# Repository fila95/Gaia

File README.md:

# GAIA
Advanced User Interfaces Course Repository

- [GAIA](#gaia)
  * [Configuration](#configuration)
    + [Action Files:](#action-files-)
    + [Actions:](#actions-)
      - [StartAction](#startaction)
          + [Available Attributes](#available-attributes)
      - [End Action](#end-action)
          + [Available Attributes](#available-attributes-1)
      - [Restart Action](#restart-action)
          + [Available Attributes](#available-attributes-2)
      - [Play Audio](#play-audio)
      - [Show Color](#show-color)
      - [Play Animation Action](#play-animation-action)
          + [Available Attributes](#available-attributes-3)
      - [Dynamic Load Action](#dynamic-load-action)
          + [Available Attributes](#available-attributes-4)
      - [Jump Action](#jump-action)
          + [Available Attributes](#available-attributes-5)
      - [Wait Input Action](#wait-input-action)
          + [Available Attributes](#available-attributes-6)
      - [Delay](#delay)
      - [Combined Action](#combined-action)
          + [Available Attributes](#available-attributes-7)
      - [Single Selection Menu Action](#single-selection-menu-action)
      - [Multiple Choice Menu Action](#multiple-choice-menu-action)
          + [Available Attributes](#available-attributes-8)

## Configuration

### Action Files:
Action Files **MUST** contain an array of actions configured as follows:

Remember that the order matters!
``` json
[
	{
		"parseIdentifier": "START",
		"attributes": {}
	},
	{
		"parseIdentifier": "END",
		"attributes": {}
	},
]
```

### Actions:
Actions are composed as follows:
``` json
{
	"parseIdentifier": "START",
	"attributes": {}
}
```

Other two *OPTIONAL* attributes can be specified:
``` json
{
	"parseIdentifier": "START",
	"attributes": {},
	"identifier": "__ID__",
	"timeout": 10
}
```

`identifier` m if specified, sets an identifier for that action so that can be used to the Skip Action.
`timeout` if specified (in seconds), kills the action after a certain amount of time.

#### StartAction
An action that identifies the game's start point.
Start and End actions should be used ONLY in the mail loadable action file!
``` json
{
	"parseIdentifier": "START",
	"attributes": {}
}
```

###### Available Attributes
No attributes are needed.

---

#### End Action
An action that identifies the game has reached the end.
Start and End actions should be used ONLY in the mail loadable action file!
``` json
{
	"parseIdentifier": "END",
	"attributes": {}
}
```

###### Available Attributes
No attributes are needed.

---

#### Restart Action
An action that restarts the entire action hierarchy!
``` json
{
	"parseIdentifier": "RESTART",
	"attributes": {}
}
```

###### Available Attributes
No attributes are needed.

---

#### Play Audio
An action that plays an audio. 
``` json
{
	"parseIdentifier": "PLAY_AUDIO",
	"attributes": {
		"path": "\root\audio_folder\audio.ogg"
	}
}
```
| Parameter 	| Type       	| Description 	|
|-----------	|------------	|-------------	|
| path | `required` 	| path should be a path for a useful audio: `\root\audio_folder\audio.ogg`|

---

#### Show Color
An action that shows a color on a dot.
Colors should be specified if different colors should be applied to different dots.
Color should be specified wether it is needed to update all colors at once.
One of those properties **MUST** be specified!
``` json
{
	"parseIdentifier": "SHOW_COLOR",
	"attributes": {
		"fade": true,
		"colors": [
			{
				"index" : 0,
				"color" : {
					"red":255,
					"green":255,
					"blue":255
				}
			},
			{
				"index" : 1,
				"color" : {
					"red":128,
					"green":128,
					"blue":128
				}
			}
		],
		"color": {
			"red":255,
			"green":255,
			"blue":255
		}
	}
}
```

| Parameter 	| Type       	| Description 	|
|-----------	|------------	|-------------	|
| colors | `required` *one* 	| `color` defines the next color to show, `index` defines the dot that will show the color  |
| color | `required` *one* 	| color sets all the dots to the same color |
| fade | `optional` 	| fade animates the transation between the previous color and the taget ones|

---

#### Play Animation Action
An action that plays an animation on the dots!
If no timeout is specified in the action's definition the action starts and ends immediately so make sure to set the `stops_at_end` key accordingly to your needs!
``` json
{
	"parseIdentifier": "PLAY_ANIMATION",
	"attributes": {
		"animation": "RAINBOW_CYCLE",
		"animation_affect_dots": true,
		"stops_at_end": true
	}
}
```

###### Available Attributes

| Parameter 	| Type       	| Description 	|
|-----------	|------------	|-------------	|
| animation | `required` 	| animation should be one of: `RAINBOW`, `RAINBOW_CYCLE`, `THEATER_CHASE_RAINBOW`|
| animation_affect_dots | `optional` 	| wether animation animates the single leds or the entire dot |
| stops_at_end | `required` 	| when action finishes set `true` if the animation should stop, otherwise set `false`|

---

#### Dynamic Load Action
An action that loads other actions from file and appends them after itself. Then goes directly to the next one.
``` json
{
	"parseIdentifier": "DYNAMIC_LOAD",
	"attributes": {
		"paths": [
			"config/blabla.action.json"
		]
	}
}
```

###### Available Attributes

| Parameter 	| Type       	| Description 	|
|-----------	|------------	|-------------	|
| paths | `required` 	| array of strings identifying one file each|

---

#### Jump Action
An action that jumps to another action given its identifier. Notice that the identifier of the other action **MUST** exist and be present in the current loaded actions hierarchy. Just specify it as you can see [here](#actions-)!
``` json
{
	"parseIdentifier": "JUMP",
	"attributes": {
		"actionIdentifier": "__ID__"
	}
}
```

###### Available Attributes

| Parameter 	| Type       	| Description 	|
|-----------	|------------	|-------------	|
| actionIdentifier | `required` 	| string that identifies another action|

---

#### Wait Input Action
An action that waits for a specified input (all of the specified are tapped) to proceed to the next action.
if `available_dot_indexes` is not specified than it waits for one input to proceed.
``` json
{
	"parseIdentifier": "WAIT_INPUT",
	"attributes": {
		"available_dot_indexes": [
			0,
			1
		]
	}
}
```

###### Available Attributes

| Parameter 	| Type       	| Description 	|
|-----------	|------------	|-------------	|
| available_dot_indexes | `optional` 	| array of integers identifying dots that are allowed to be tapped|

---

#### Delay 
A delay between 2 action.
Timeout should be in **seconds**.
``` json
{
	"parseIdentifier": "DELAY",
	"attributes": {
		"delay": 10
	}
}
```
| Parameter 	| Type       	| Description 	|
|-----------	|------------	|-------------	|
| delay | `required` 	| delay in seconds between 2 actions |

---

#### Combined Action 
Defines multiple action to be executed together.
``` json
{
	"parseIdentifier": "COMBINED",
	"timeout": 10,
	"attributes": {
		"actions": [
			{
				"parseIdentifier": "PLAY_ANIMATION",
				"attributes": {
					"animation": "RAINBOW_CYCLE",
					"animation_affect_dots": true,
					"stops_at_end": true
				}
			},
			{
				"parseIdentifier": "PLAY_AUDIO",
				"attributes": {
					"path": "\root\audio_folder\audio.ogg"
				}
			}
		],
		"policy" : "EXIT_TIMEOUT"
	}
}
```

###### Available Attributes
| Parameter 	| Type       	| Description 	|
|-----------	|------------	|-------------	|
| actions | `required` 	| actions to be executed together. Actions such as `DYNAMIC_LOAD`, `END`, `START`, `RESTART`, `JUMP` are automatically ignored if added! |
| policy | `required` 	| two types of policies: `WAIT_ALL` (waits all actions to be terminated before continuing) ,  `WAIT_FIRST` (when first is completed go to the next action), `EXIT_TIMEOUT` (kills this entire group when timeout occurs)|

---

#### Single Selection Menu Action
A menu which makes people choose between different options. When one is selected its actions are executed!

Options **MUST** contain as many options as dots are in the system!

``` json
{
	"parseIdentifier": "SINGLE_CHOICE_MENU",
	"timeout": 10,
	"attributes": {
		"options": [
			{
				"actions" : [],
				"color" : {
					"red" : "25",
					"green" : "25",
					"blue" : "25"
				}
			}
			{
				"actions" : [],
				"color" : {
					"red" : "25",
					"green" : "25",
					"blue" : "25"
				}
			}
			{
				"actions" : [],
				"color" : {
					"red" : "25",
					"green" : "25",
					"blue" : "25"
				}
			}
			{
				"actions" : [],
				"color" : {
					"red" : "25",
					"green" : "25",
					"blue" : "25"
				}
			}
		],
		"timeout_actions": []
			
	}
}
```

| Parameter 	| Type       	| Description 	|
|-----------	|------------	|-------------	|
| options | `required` 	| options available: `actions` is an array of action objects, `color` is the color associated with that action! Options **MUST** contain as many options as dots are in the system!  |
| timeout_actions | `required` | action object array to be executed after a timeout |

---

#### Multiple Choice Menu Action 
Defines a menu with different options and when one sequence is correctly inserted than it triggers its actions, otherwise it triggers a wrong choices defined action!

Options **MUST** contain as many options as dots are in the system!

``` json
{
	"parseIdentifier": "MULTIPLE_CHOICE_MENU",
	"timeout": 10,
	"attributes": {
		"options": [
			{ "red": 255, "green": 255, "blue": 255 },
			{ "red": 255, "green": 255, "blue": 255 },
			{ "red": 255, "green": 255, "blue": 255 },
			{ "red": 255, "green": 255, "blue": 255 }
		],
		"allowed_sequences": [
			{ 
				"actions": [],
				"chosen_options": [0, 3]
			}
		],
		"wrong_sequence_actions": [],
		"abort_actions": [],
		"time_between_choices": 1
	}
}
```

###### Available Attributes
| Parameter 	| Type       	| Description 	|
|-----------	|------------	|-------------	|
| options | `required` 	| contains an array of colors that will be shown on the dots as choices. The number of options **MUST** be equal to the number of dots! |
| allowed_sequences | `required` | array of items containing a list of actions to be executed when whose options are selected!, `chosen_options` should be an array of integers which reflects the `options` described above. **Remember**: order matters! |
| wrong_sequence_actions | `required` | Sequence of actions that are executed if a not allowed sequence if inserted! |
| abort_actions | `required` | Sequence of actions that are executed when timeout fires and no choice is taken! |
| time_between_choices | `optional` | Maximum time allowed between each tap on dots! if timeout fires up than it checks the inserted sequence and does its things according to the correctness of it. |

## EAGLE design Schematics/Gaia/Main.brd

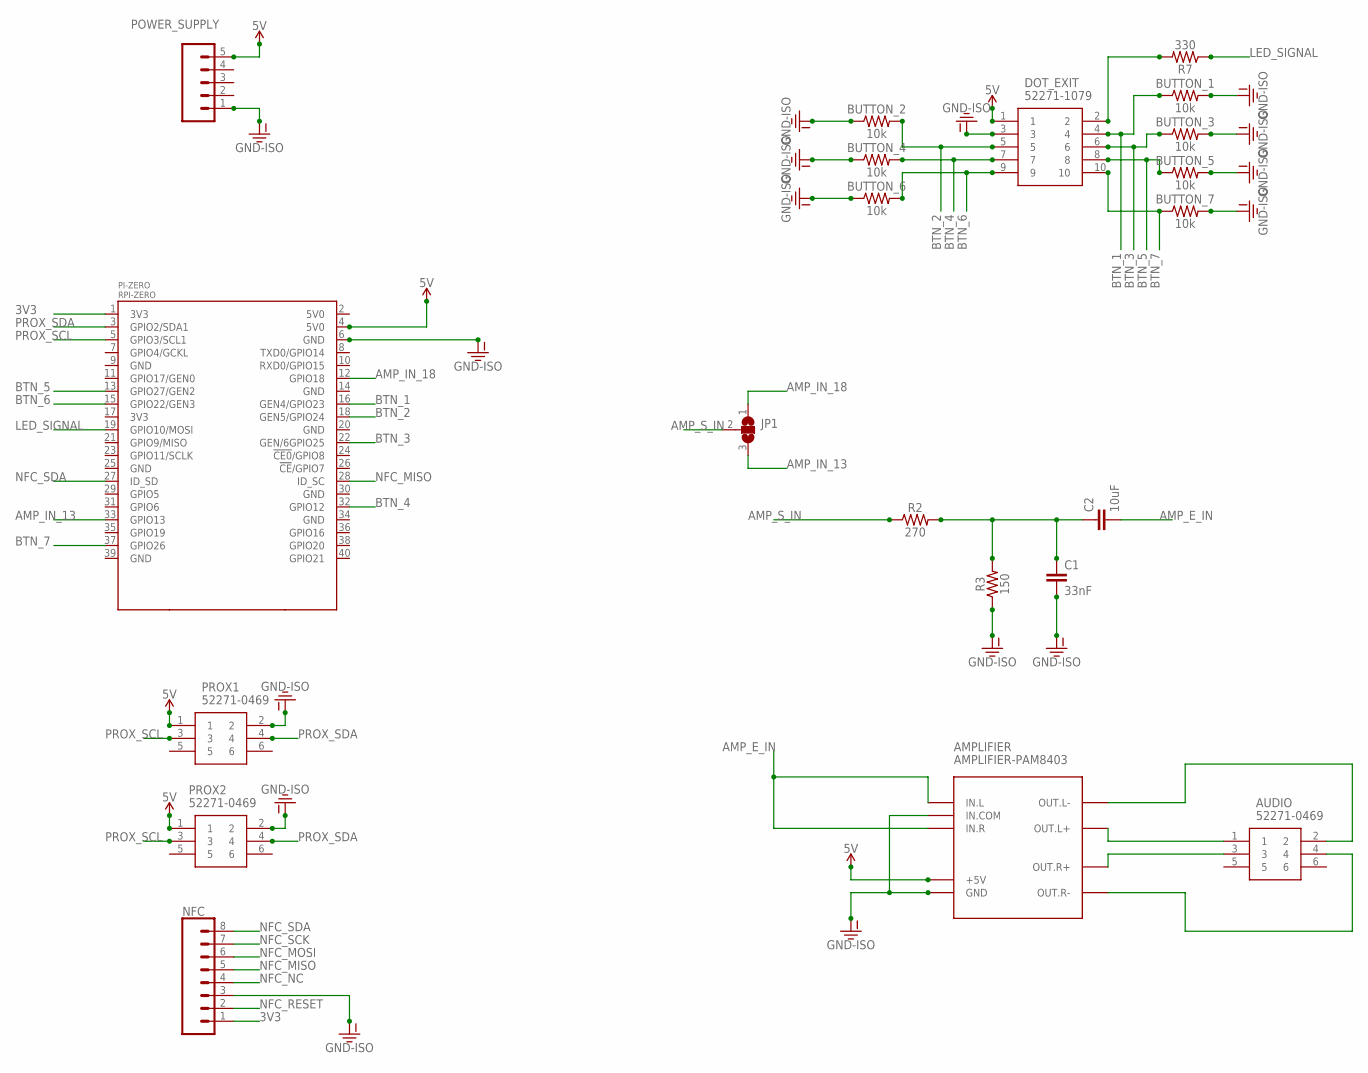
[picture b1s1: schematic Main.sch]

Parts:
AMPLIFIER: AMPLIFIER-PAM8403
AUDIO: 52271-0469; MOLEX_52271-0469
BUTTON_1, BUTTON_2, BUTTON_3, BUTTON_4, BUTTON_5, BUTTON_6, BUTTON_7: 10k; AXIAL-0.3
C1: 33nF; CAP-PTH-10MM
C2: 10uF; CAP-PTH-10MM
DOT_EXIT: 52271-1079
JP1: SJ2W; SJ_2
NFC: CONN_08"; 1X08
PI-ZERO: RPI-ZERO; RASPBERRYPI_BASTELSTUBE_V13_RASPI_BOARD_B+_FULL
POWER_SUPPLY: CONN_05; 1X05
PROX1, PROX2: 52271-0469; MOLEX_52271-0469
R2: 270; AXIAL-0.3
R3: 150; AXIAL-0.3
R7: 330; AXIAL-0.3

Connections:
3V3: NFC.1, PI-ZERO.1 (3V3)
5V: AMPLIFIER.+5V, DOT_EXIT.1, PI-ZERO.4 (5V0), POWER_SUPPLY.5, PROX1.1, PROX2.1
AMP_E_IN: AMPLIFIER.IN.L, AMPLIFIER.IN.R, C2.2
AMP_IN_13: JP1.3, PI-ZERO.33 (GPIO13)
AMP_IN_18: JP1.1, PI-ZERO.12 (GPIO18)
AMP_S_IN: JP1.2, R2.P$1 (1)
BTN_1: BUTTON_1.P$1 (1), DOT_EXIT.4, PI-ZERO.16 (GEN4/GPIO23)
BTN_2: BUTTON_2.P$2 (2), DOT_EXIT.5, PI-ZERO.18 (GEN5/GPIO24)
BTN_3: BUTTON_3.P$1 (1), DOT_EXIT.6, PI-ZERO.22 (GEN/6GPIO25)
BTN_4: BUTTON_4.P$2 (2), DOT_EXIT.7, PI-ZERO.32 (GPIO12)
BTN_5: BUTTON_5.P$1 (1), DOT_EXIT.8, PI-ZERO.13 (GPIO27/GEN2)
BTN_6: BUTTON_6.P$2 (2), DOT_EXIT.9, PI-ZERO.15 (GPIO22/GEN3)
BTN_7: BUTTON_7.P$1 (1), DOT_EXIT.10, PI-ZERO.37 (GPIO26)
GND-ISO: AMPLIFIER.GND, AMPLIFIER.IN.COM, BUTTON_1.P$2 (2), BUTTON_2.P$1 (1), BUTTON_3.P$2 (2), BUTTON_4.P$1 (1), BUTTON_5.P$2 (2), BUTTON_6.P$1 (1), BUTTON_7.P$2 (2), C1.2, DOT_EXIT.3, NFC.3, PI-ZERO.6 (GND), POWER_SUPPLY.1, PROX1.2, PROX2.2, R3.P$1 (1)
LED_SIGNAL: PI-ZERO.19 (GPIO10/MOSI), R7.P$1 (1)
unnamed: DOT_EXIT.2, R7.P$2 (2)
unnamed: AMPLIFIER.OUT.L-, AUDIO.2
unnamed: AMPLIFIER.OUT.L+, AUDIO.1
unnamed: C1.1, C2.1, R2.P$2 (2), R3.P$2 (2)
unnamed: AMPLIFIER.OUT.R+, AUDIO.3
unnamed: AMPLIFIER.OUT.R-, AUDIO.4
NFC_MISO: NFC.5, PI-ZERO.28 (ID_SC)
NFC_MOSI: NFC.6
NFC_NC: NFC.4
NFC_RESET: NFC.2
NFC_SCK: NFC.7
NFC_SDA: NFC.8, PI-ZERO.27 (ID_SD)
PROX_SCL: PI-ZERO.5 (GPIO3/SCL1), PROX1.3, PROX2.3
PROX_SDA: PI-ZERO.3 (GPIO2/SDA1), PROX1.4, PROX2.4

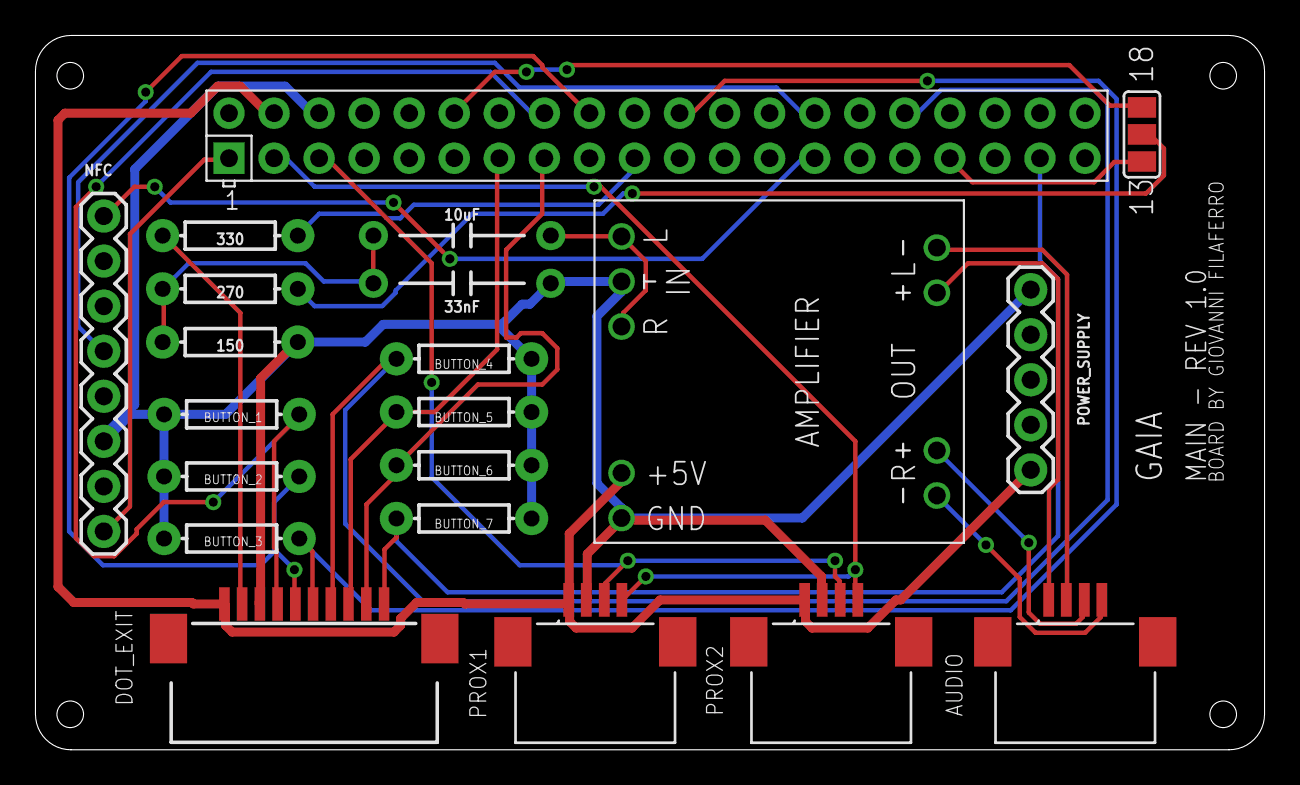
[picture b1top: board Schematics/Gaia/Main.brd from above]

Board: 2 copper layers, 69.3 x 40.3 mm, 21 parts (0 on the bottom side), 25 nets.

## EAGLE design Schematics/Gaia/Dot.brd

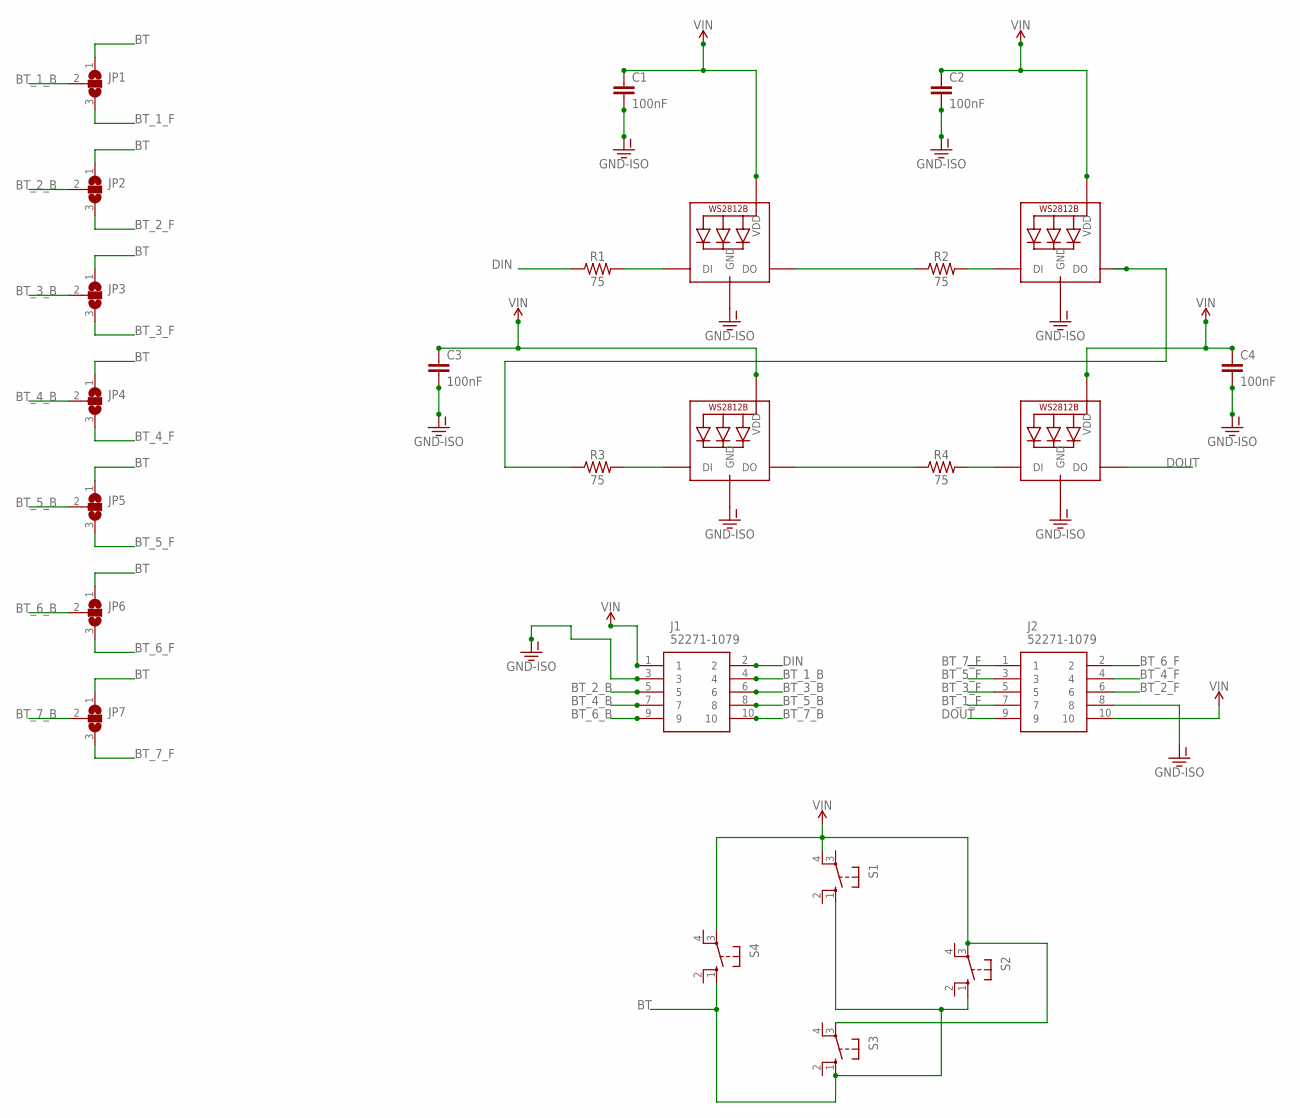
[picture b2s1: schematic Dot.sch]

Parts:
C1, C2, C3, C4: 100nF; 0603
J1, J2: 52271-1079
JP1, JP2, JP3, JP4, JP5, JP6, JP7: SJ2W; SJ_2
LED1, LED2, LED3, LED4: WS2812B5050; WS2812B
R1, R2, R3, R4: 75; 0603
S1, S2, S3, S4: 10-XX; B3F-10XX

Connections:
BT: JP1.1, JP2.1, JP3.1, JP4.1, JP5.1, JP6.1, JP7.1, S1.1 (S), S2.1 (S), S3.1 (S), S4.1 (S)
BT_1_B: J1.4, JP1.2
BT_1_F: J2.7, JP1.3
BT_2_B: J1.5, JP2.2
BT_2_F: J2.6, JP2.3
BT_3_B: J1.6, JP3.2
BT_3_F: J2.5, JP3.3
BT_4_B: J1.7, JP4.2
BT_4_F: J2.4, JP4.3
BT_5_B: J1.8, JP5.2
BT_5_F: J2.3, JP5.3
BT_6_B: J1.9, JP6.2
BT_6_F: J2.2, JP6.3
BT_7_B: J1.10, JP7.2
BT_7_F: J2.1, JP7.3
DIN: J1.2, R1.1
DOUT: J2.9, LED4.2-DOUT (DO)
GND-ISO: C1.2, C2.2, C3.2, C4.2, J1.3, J2.8, LED1.3-GND (GND), LED2.3-GND (GND), LED3.3-GND (GND), LED4.3-GND (GND)
unnamed: LED2.2-DOUT (DO), R3.1
unnamed: LED1.4-DIN (DI), R1.2
unnamed: LED1.2-DOUT (DO), R2.1
unnamed: LED2.4-DIN (DI), R2.2
unnamed: LED3.4-DIN (DI), R3.2
unnamed: LED3.2-DOUT (DO), R4.1
unnamed: LED4.4-DIN (DI), R4.2
VIN: C1.1, C2.1, C3.1, C4.1, J1.1, J2.10, LED1.1-VDD (VDD), LED2.1-VDD (VDD), LED3.1-VDD (VDD), LED4.1-VDD (VDD), S1.4 (P1), S2.3, S3.3, S4.3

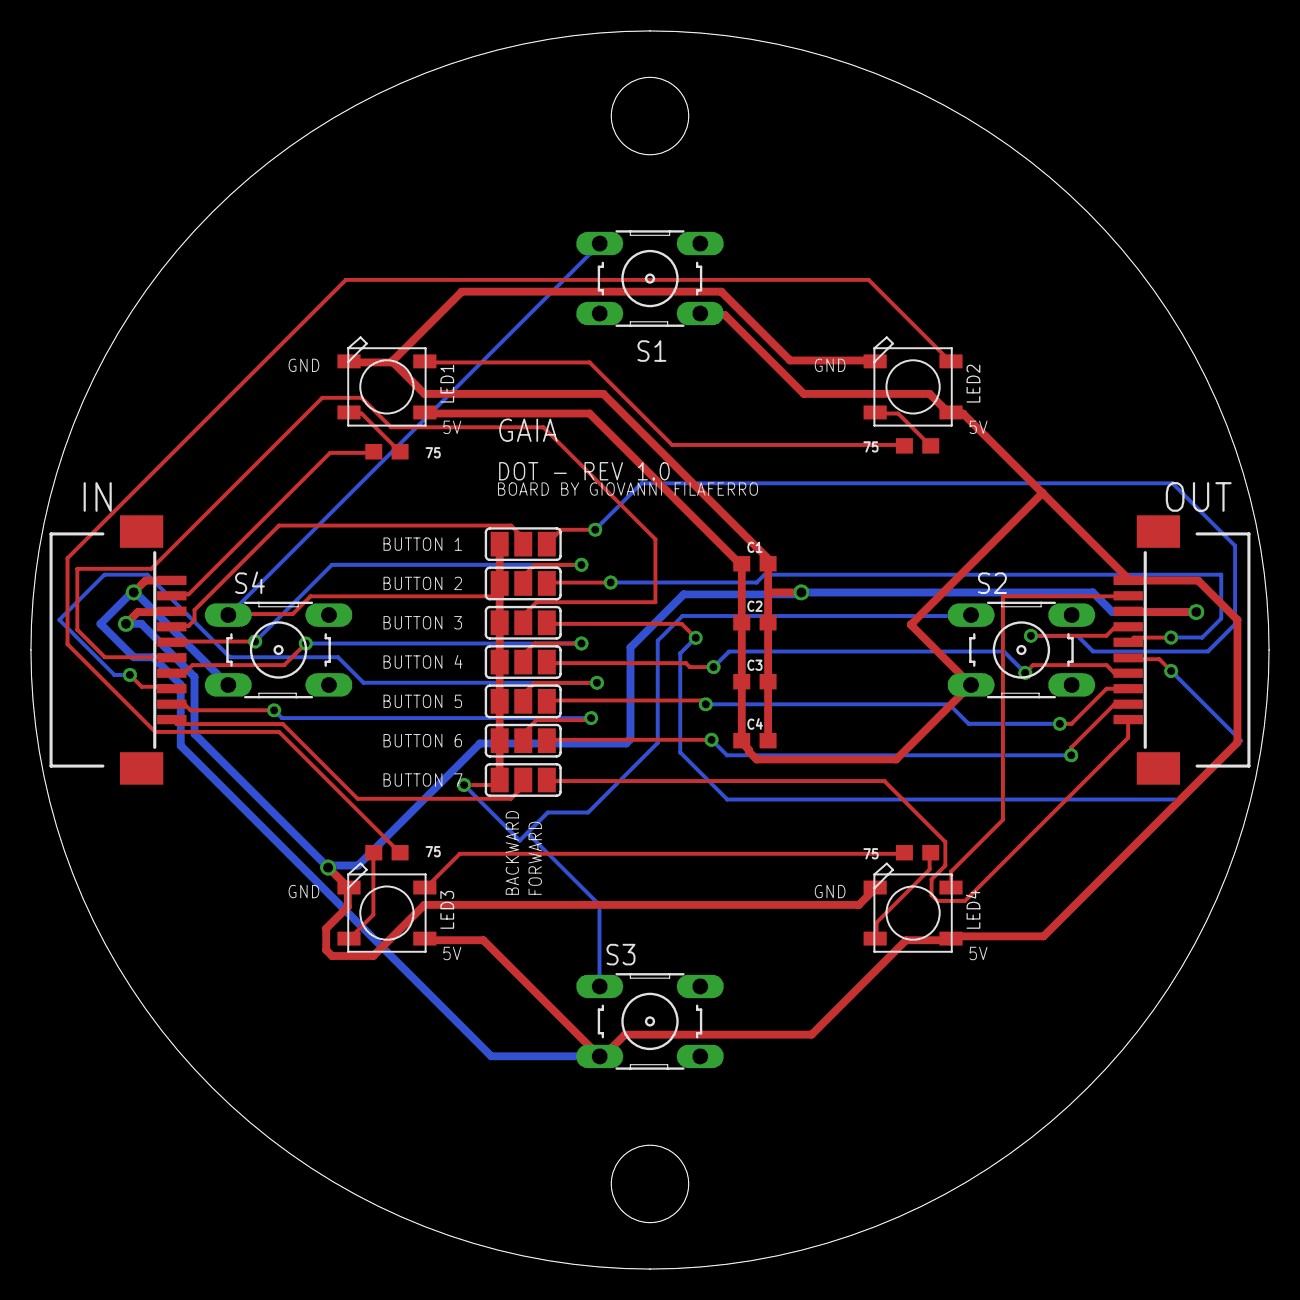
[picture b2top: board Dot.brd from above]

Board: 2 copper layers, 80.0 x 80.0 mm, 25 parts (0 on the bottom side), 26 nets.

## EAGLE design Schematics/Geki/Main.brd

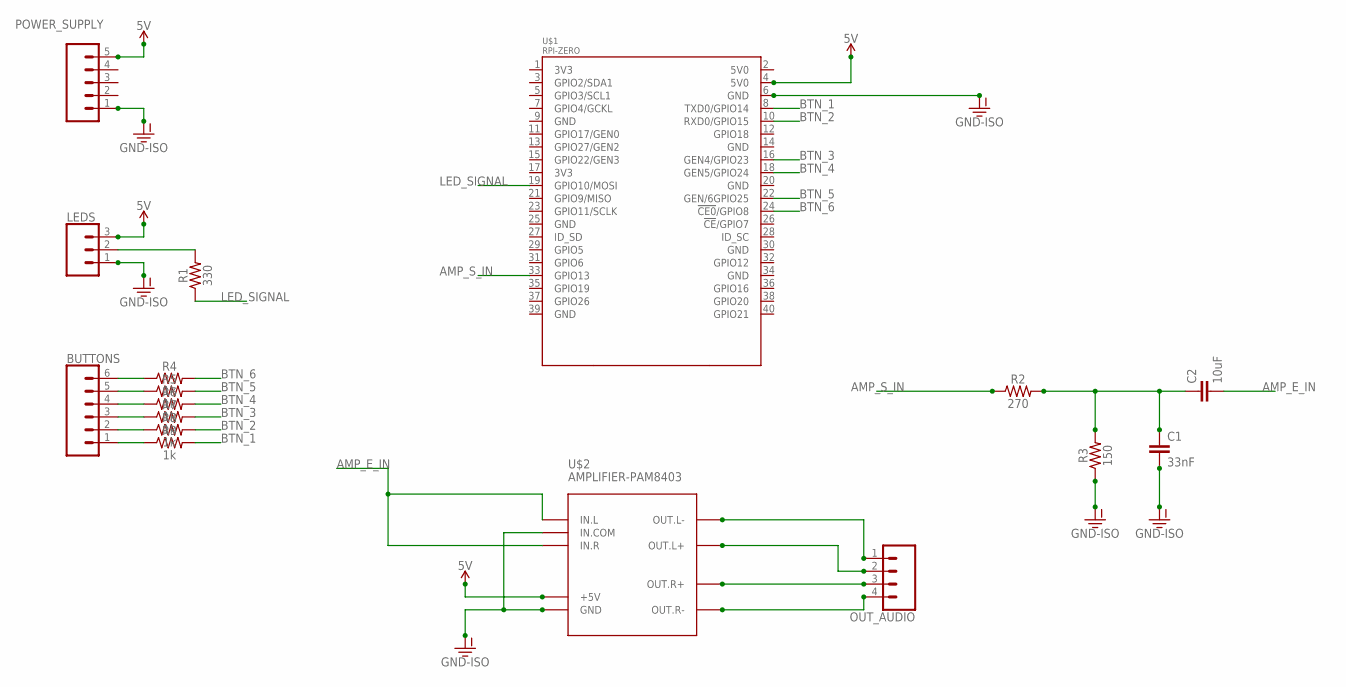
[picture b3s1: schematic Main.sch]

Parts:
BUTTONS: CONN_06SILK_FEMALE_PTH; 1X06
C1: 33nF; CAP-PTH-10MM
C2: 10uF; CAP-PTH-10MM
LEDS: CONN_03; 1X03
OUT_AUDIO: CONN_04; 1X04
POWER_SUPPLY: CONN_05; 1X05
R1: 330; AXIAL-0.3
R2: 270; AXIAL-0.3
R3: 150; AXIAL-0.3
R4, R5, R6, R7, R8, R9: 1k; AXIAL-0.3
U$1: RPI-ZERO; RASPBERRYPI_BASTELSTUBE_V13_RASPI_BOARD_B+_FULL
U$2: AMPLIFIER-PAM8403

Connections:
5V: LEDS.3, POWER_SUPPLY.5, U$1.4 (5V0), U$2.+5V
AMP_E_IN: C2.2, U$2.IN.L, U$2.IN.R
AMP_S_IN: R2.P$1 (1), U$1.33 (GPIO13)
BTN_1: R9.P$2 (2), U$1.8 (TXD0/GPIO14)
BTN_2: R8.P$2 (2), U$1.10 (RXD0/GPIO15)
BTN_3: R7.P$2 (2), U$1.16 (GEN4/GPIO23)
BTN_4: R6.P$2 (2), U$1.18 (GEN5/GPIO24)
BTN_5: R5.P$2 (2), U$1.22 (GEN/6GPIO25)
BTN_6: R4.P$2 (2), U$1.24 (!CE0!/GPIO8)
GND-ISO: C1.2, LEDS.1, POWER_SUPPLY.1, R3.P$1 (1), U$1.6 (GND), U$2.GND, U$2.IN.COM
LED_SIGNAL: R1.P$1 (1), U$1.19 (GPIO10/MOSI)
unnamed: LEDS.2, R1.P$2 (2)
unnamed: OUT_AUDIO.1, U$2.OUT.L-
unnamed: OUT_AUDIO.2, U$2.OUT.L+
unnamed: C1.1, C2.1, R2.P$2 (2), R3.P$2 (2)
unnamed: OUT_AUDIO.4, U$2.OUT.R-
unnamed: OUT_AUDIO.3, U$2.OUT.R+
unnamed: BUTTONS.6, R4.P$1 (1)
unnamed: BUTTONS.5, R5.P$1 (1)
unnamed: BUTTONS.4, R6.P$1 (1)
unnamed: BUTTONS.3, R7.P$1 (1)
unnamed: BUTTONS.2, R8.P$1 (1)
unnamed: BUTTONS.1, R9.P$1 (1)

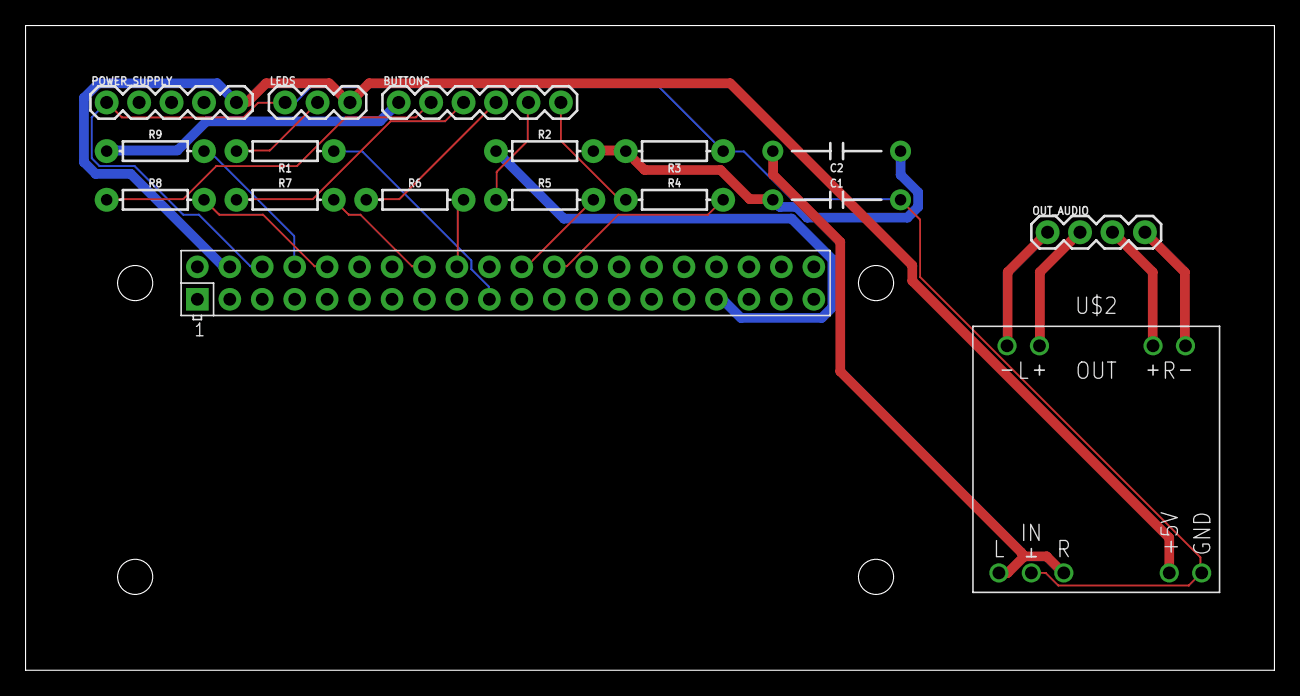
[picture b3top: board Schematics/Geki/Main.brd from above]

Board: 2 copper layers, 97.8 x 50.5 mm, 17 parts (0 on the bottom side), 23 nets.

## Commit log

2018-11-13 upload to raspberry and deploy scripts prepared, now need to write the deploy service helper
2018-11-14 fix on upload scripts, ready to test on real raspberry
2018-11-14 adding wifi update template for rasspberry
2018-11-14 adding pinout board for raspberry pi zero w to simplify pin occupations just overwriting the image with marked the pin that will be used for their purpose
2018-11-14 fixed scripts
2018-11-14 fixing scripts, now services restart after reboot, image populated with occupied led pin, ironman service added, that will become the main light disk manager, now it's just a sample
2018-11-14 first implemetation of some steps the algorithm
2018-11-15 Extracted some code from main script to make an utils script
2018-11-15 minor fixes and pinout, jsbeautify added to beautify files all same way
2018-11-16 scripts fixes, added disabled folder, added geki components (Dot is the entire disk with button, dotmanager manages dots), fully working with callbacks ;)
2018-11-17 fixes on manager, adding brightness modifier, added 3d stl files for new dot version ;)
2018-11-17 script in prova da modificare
2018-11-17 fix 3d files
2018-11-17 added cap stl file (pressable area of the dots)
2018-11-17 fixed upload first install script
2018-11-17 install fix, stl files fixed
2018-11-18 new stl file for the cap of the dots
2018-11-18 first install script fixed
2018-11-18 main plate fix led cutout
2018-11-19 fixes, noew plate, dotManager added conveniences
2018-11-19 added logging to dotmanager and dot
2018-11-19 clamping values for colors
2018-11-19 refactor, added convenience methods
2018-11-19 adding more conveniences
2018-11-19 Speaker and SoundManager (for Giovanni)
2018-11-19 Added StoriesColorManager, rewritten main scritp (geki_2.py), reorganized directories
    Code not yet tested
2018-11-20 Fixed some errors, improved code readability
2018-11-20 giga refactoring, adding fade colors to dots, now tested and working
2018-11-21 small refactor
2018-11-21 big refactor, added animations to DotManager to chase, now they affect the single LED for test purposes, then they'll affect the dots
2018-11-21 small fixes on types
2018-11-21 fixes
2018-11-21 small fix on test script
2018-11-21 fixes on animation stopping
2018-11-21 removing still unavailable animation
2018-11-21 restoring rainbow cycle
2018-11-21 Continuato main script
2018-11-21 fixes on animations
2018-11-21 minor error fixed
2018-11-21 type fixes and install.sh changes for first_install
2018-11-21 refactor and fix
2018-11-22 new 3d files (hopefully the last ones)
2018-11-22 Moved constants.py
2018-11-22 Implemented part of the algorithm of the game
2018-11-22 filter button pin press with glitch filter
2018-11-25 Completed game logic, fixed syntax errors, fixed some bugs
    Tested up to first sound emission. Unsolved bug in quitting (it quits execution fine, but needs reboot to be re-executed, otherwise it makes noise instead of the right sound)
2018-11-26 New stl files
2018-11-26 fixes, cleanup, refactor, added ability to choose wether animation affects leds individually or dots ;)
2018-11-26 ironman should now be fixed
2018-11-26 imports fix
2018-11-26 fix imports
2018-11-26 Fixed syntax
2018-11-26 generic fixes, ironman, upload scripts, service definitions
2018-11-26 Updated audio file
2018-11-26 generic fixes
2018-11-26 fixes on services, install
2018-11-26 upload geki_2 with started rewriting code
2018-11-26 Story
2018-11-27 fixes and improvements
2018-11-28 Add new class (ChapterPlayer)
2018-11-29 color available
2018-11-30 fixes on scripts, geki story improvements, code optimizations
2018-11-30 fixes, game logic nearly finished
2018-11-30 add some return
2018-11-30 GAME LOGIC DONE!!! (Just need to test it on device)
2018-11-30 merge
2018-11-30 global fixes
2018-12-01 Big fixes around, game logic half tested, need to test audio, changed led pins, updated schema, updated geki_2 files
2018-12-01 install script updated
2018-12-01 Audio circuit schematics added
2018-12-03 eagle schematics added
2018-12-04 entire new game login files, refactor, fixes, removed unused files, fixes
2018-12-04 more
2018-12-04 fixes and additions
2018-12-05 added sound action, fixes, improvements
2018-12-05 added actions schema, cleanup around
2018-12-05 new map
2018-12-05 gitignore edit
2018-12-05 fixes, adding actions, readme
2018-12-05 play animation now done! Readme updated, removed stories picker
2018-12-05 added dynamic load actions, updated actions map, updated readme
2018-12-05 readme
2018-12-05 jump action added, updated readme, updated actions map
2018-12-05 added wait input action, update readme, updated actions map
2018-12-05 show color
2018-12-05 delay and start concurrent
2018-12-05 update readme, fixes
2018-12-05 Combined action added, updated readme, fixes around, moved timers (action dependent now)
2018-12-05 action map, readme
2018-12-05 Single
2018-12-05 fixes, refactor, added method to parse single action from json
2018-12-05 started multiple choices implementation
2018-12-06 New 3d models, main plate and bottom tested, trying out the cap now
2018-12-06 readme for multiple choices
2018-12-06 multiple choices menu action fixes and now implemented
2018-12-06 refactor single choice menu, readme fixes and additions
2018-12-06 name changed
2018-12-06 new cap 3d
2018-12-08 Added audio files for one possible story
    First version of audio files, should be good for Demos.
2018-12-09 fixes, cleanup, new schematics, new 3d files, readme edits, fixes on scripts
2018-12-09 fixes and refactor
2018-12-09 generic fixes on scripts, now audio callbacks really work, audio plays
2018-12-09 new schematic fixes and install script fix
2018-12-10 Documents for the pitch and music jingle added
2018-12-11 actions for first story added and completed
2018-12-11 fixes, cleanup
2018-12-11 fixes, modifications
2018-12-12 Added source file for documents, updated pdfs to last version, updated jingle.wav
2018-12-12 fixes, sounds
2018-12-12 new style pitch
2018-12-12 presentation slide missing added
2018-12-12 last fixes
2018-12-12 fixes on multiple choice menu, fixes on combined actions (added check when an action finishes)
2018-12-13 Pitch name updated, deleted old files
2018-12-13 new color
2018-12-13 presentation
2018-12-13 fixes additions
2018-12-18 game
2018-12-18 action guide
2018-12-26 new schematics, new stuff, fixes and improvements
2019-01-21 new 3d files,renders, new schematics, exports, fixes (initial ground for thesis)
2019-01-22 new control box
2019-01-25 fixers, additions, students evaluation build
2019-02-05 documents for final presentation of the course
2019-02-05 Final presentation Corrected
2019-02-05 final presentation export pdf
2019-02-06 last correction
2019-02-13 last docs

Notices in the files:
parts and their libraries:
SparkFun-Capacitors: Licensing: Creative Commons ShareAlike 4.0 International - https://creativecommons.org/licenses/by-sa/4.0
diy-modules: Released under the Creative Commons Attribution 4.0 International License: http://creativecommons.org/licenses/by/4.0
